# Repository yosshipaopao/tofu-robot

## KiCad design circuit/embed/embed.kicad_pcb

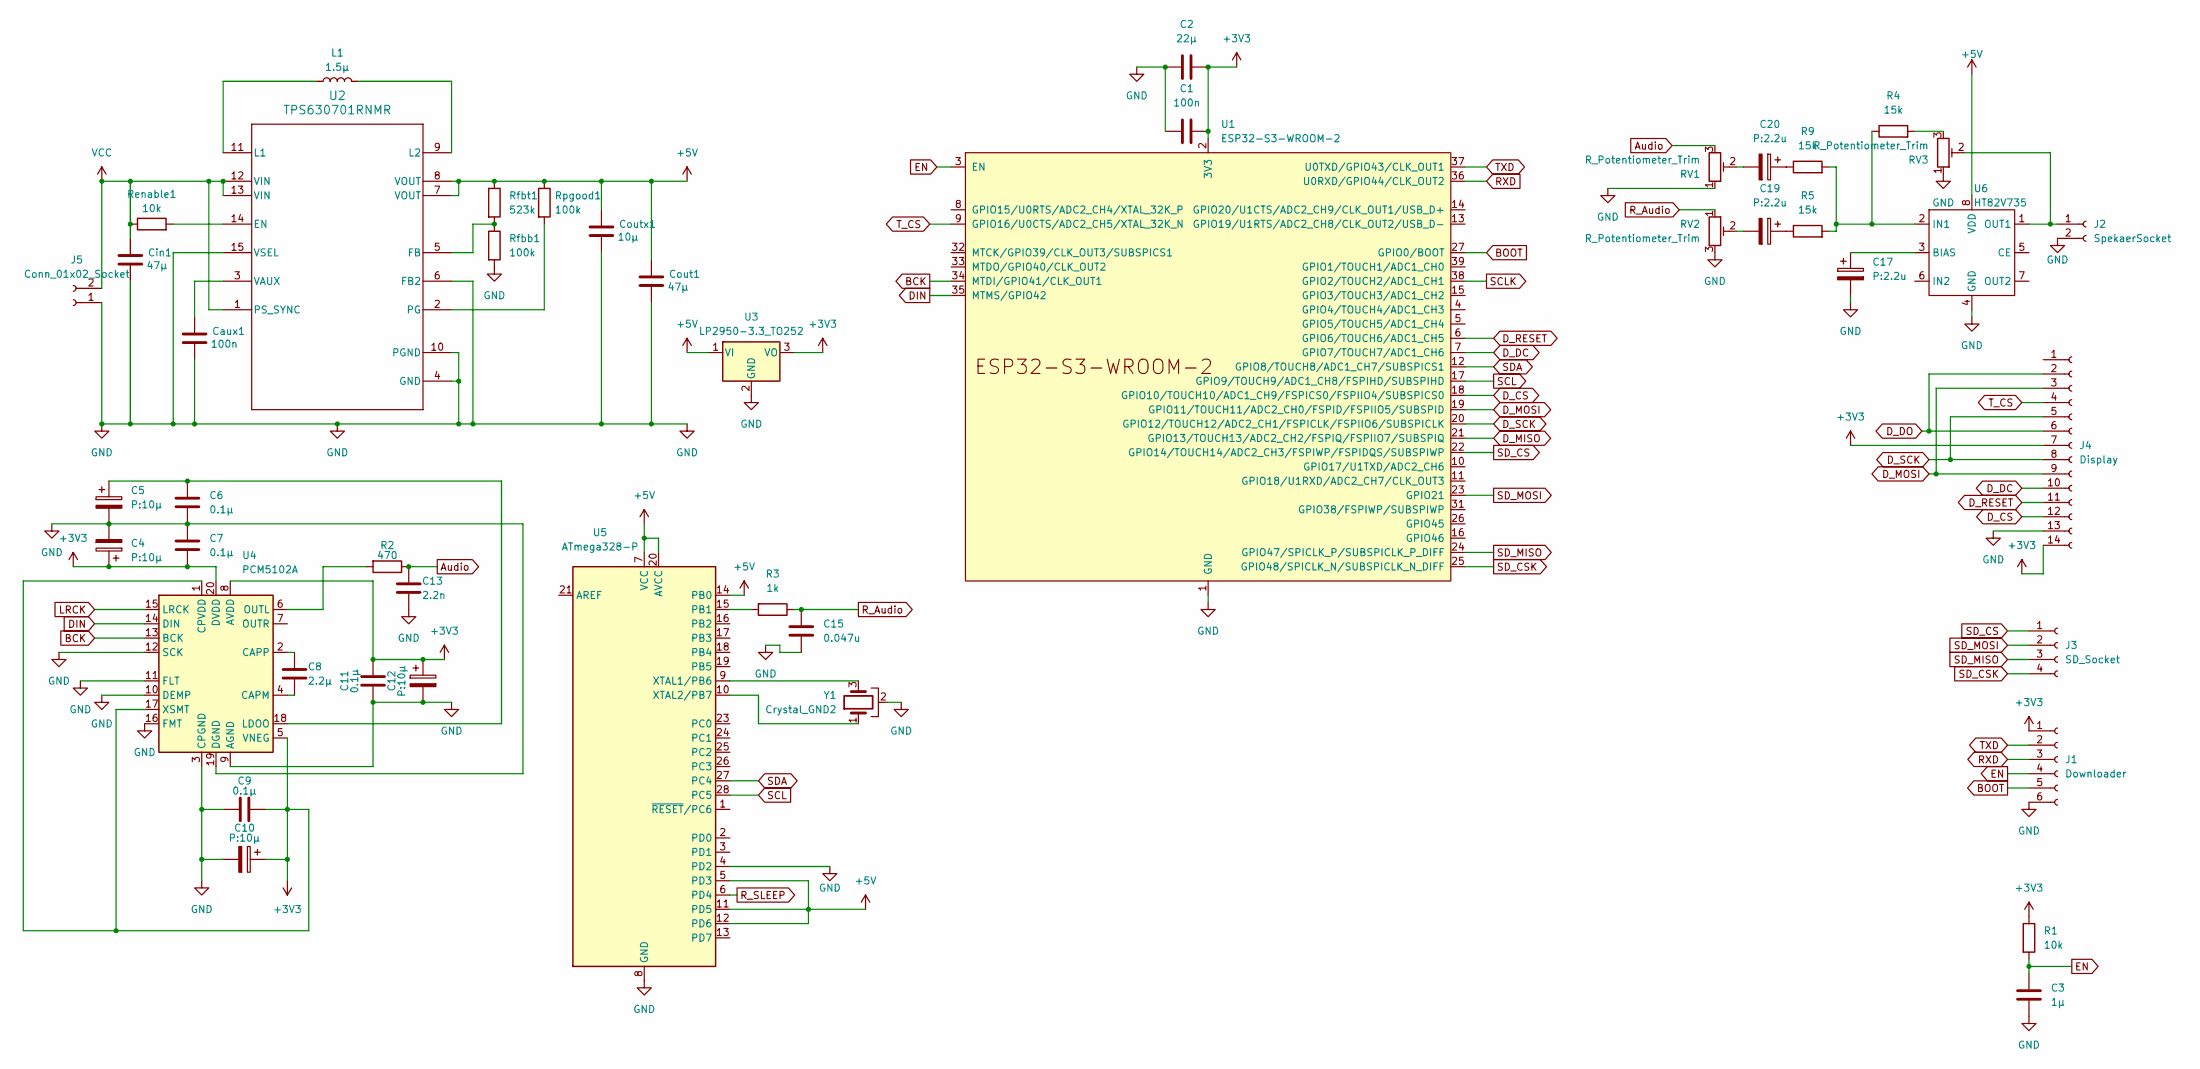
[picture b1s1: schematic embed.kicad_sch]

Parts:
C1: 100n; C_0402_1005Metric
C2: 22μ; C_0603_1608Metric
C3: 1μ; C_0402_1005Metric
C4, C5, C10, C12: P:10μ; CP_Elec_3x5.4
C6, C7, C9, C11: 0.1μ; C_0402_1005Metric
C8: 2.2μ; C_0504_1310Metric
C13: 2.2n; C_0402_1005Metric
C15: 0.047u; C_0402_1005Metric
C17, C19, C20: P:2.2u; CP_Elec_4x5.4
Caux1: 100n; C_0402_1005Metric
Cin1: 47μ; C_1210_3225Metric
Cout1: 47μ; C_1210_3225Metric
Coutx1: 10μ; C_0603_1608Metric
J1: Downloader; PinSocket_1x06_P2.54mm_Vertical
J2: SpekaerSocket; PinSocket_1x02_P2.54mm_Vertical
J3: SD_Socket; PinSocket_1x04_P2.54mm_Vertical
J4: Display; PinSocket_1x14_P2.54mm_Vertical
J5: Conn_01x02_Socket; PinHeader_1x02_P2.54mm_Vertical
L1: 1.5μ; L_Bourns_SRN8040TA
R1: 10k; R_0603_1608Metric
R2: 470; R_2010_5025Metric
R3: 1k; R_1210_3225Metric
R4, R5, R9: 15k; R_0603_1608Metric
RV1, RV2, RV3: R_Potentiometer_Trim; Potentiometer_Bourns_PRS11S_Vertical
Renable1: 10k; R_0201_0603Metric
Rfbb1: 100k; R_0603_1608Metric
Rfbt1: 523k; R_0603_1608Metric
Rpgood1: 100k; R_0603_1608Metric
U1: ESP32-S3-WROOM-2
U2: TPS630701RNMR; RNM0015A
U3: LP2950-3.3_TO252; TO-252-2
U4: PCM5102A; TSSOP-20_4.4x6.5mm_P0.65mm
U5: ATmega328-P; DIP-28_W7.62mm
U6: HT82V735; SOP8
Y1: Crystal_GND2; Resonator_Murata_CSTLSxxxX-3Pin_W5.5mm_H3.0mm

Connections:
+3V3: C1.1, C2.1, C4.1, C7.2, C9.1, C10.1, C11.1, C12.1, J1.1, J4.7, J4.14, R1.1, U1.2 (3V3), U3.3 (VO), U4.1 (CPVDD), U4.5 (VNEG), U4.8 (AVDD), U4.17 (XSMT), U4.20 (DVDD)
+5V: Cout1.1, Coutx1.1, Rfbt1.1, Rpgood1.1, U2.7 (VOUT), U2.8 (VOUT), U3.1 (VI), U5.5 (PD3), U5.7 (VCC), U5.11 (PD5), U5.12 (PD6), U5.14 (PB0), U5.20 (AVCC), U6.8 (VDD)
Audio: C13.1, R2.1, RV1.3
BCK: U1.34 (MTDI/GPIO41/CLK_OUT1), U4.13 (BCK)
BOOT: J1.5, U1.27 (GPIO0/BOOT)
DIN: U1.35 (MTMS/GPIO42), U4.14 (DIN)
D_CS: J4.12, U1.18 (GPIO10/TOUCH10/ADC1_CH9/FSPICS0/FSPIIO4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)
D_DC: J4.10, U1.7 (GPIO7/TOUCH7/ADC1_CH6)
D_DO: J4.2, J4.6
D_MISO: U1.21 (GPIO13/TOUCH13/ADC2_CH2/FSPIQ/FSPIIO7/S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)
D_MOSI: J4.3, J4.9, U1.19 (GPIO11/TOUCH11/ADC2_CH0/FSPID/FSPIIO5/S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)
D_RESET: J4.11, U1.6 (GPIO6/TOUCH6/ADC1_CH5)
D_SCK: J4.5, J4.8, U1.20 (GPIO12/TOUCH12/ADC2_CH1/FSPICLK/FSPIIO6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)
EN: C3.1, J1.4, R1.2, U1.3 (EN)
GND: C1.2, C2.2, C3.2, C4.2, C5.2, C6.2, C7.1, C9.2, C10.2, C11.2, C12.2, C13.2, C15.1, C17.2, Caux1.2, Cin1.2, Cout1.2, Coutx1.2, J1.6, J2.2, J4.13, J5.1, RV1.1, RV2.3, RV3.1, Rfbb1.2, U1.1 (GND), U1.40 (GND), U1.41 (GND), U2.4 (GND), U2.6 (FB2), U2.10 (PGND), U2.15 (VSEL), U3.2 (GND), U4.3 (CPGND), U4.9 (AGND), U4.10 (DEMP), U4.11 (FLT), U4.12 (SCK), U4.16 (FMT), U4.19 (DGND), U5.4 (PD2), U5.8 (GND), U5.22 (GND), U6.4 (GND), Y1.2
LRCK: U4.15 (LRCK)
unnamed: C19.1, R5.1
unnamed: C19.2, RV2.2
unnamed: C20.1, R9.1
unnamed: C20.2, RV1.2
unnamed: J2.1, RV3.2, U6.1 (OUT1)
unnamed: R4.2, RV3.3
unnamed: Renable1.2, U2.14 (EN)
unnamed: Rfbb1.1, Rfbt1.2, U2.5 (FB)
unnamed: L1.1, U2.11 (L1)
unnamed: L1.2, U2.9 (L2)
unnamed: Rpgood1.2, U2.2 (PG)
unnamed: Caux1.1, U2.3 (VAUX)
unnamed: C8.2, U4.4 (CAPM)
unnamed: C8.1, U4.2 (CAPP)
unnamed: C5.1, C6.1, U4.18 (LDOO)
unnamed: R2.2, U4.6 (OUTL)
unnamed: R3.2, U5.15 (PB1)
unnamed: U5.9 (XTAL1/PB6), Y1.3
unnamed: U5.10 (XTAL2/PB7), Y1.1
unnamed: C17.1, U6.3 (BIAS)
unnamed: R4.1, R5.2, R9.2, U6.2 (IN1)
RXD: J1.3, U1.36 (U0RXD/GPIO44/CLK_OUT2)
R_Audio: C15.2, R3.1, RV2.1
R_SLEEP: U5.6 (PD4)
SCL: U1.17 (GPIO9/TOUCH9/ADC1_CH8/FSPIHD/SUBSPIHD), U5.28 (PC5)
SCLK: U1.38 (GPIO2/TOUCH2/ADC1_CH1)
SDA: U1.12 (GPIO8/TOUCH8/ADC1_CH7/SUBSPICS1), U5.27 (PC4)
SD_CS: J3.1, U1.22 (GPIO14/TOUCH14/ADC2_CH3/FSPIWP/FSPIDQS/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)
SD_CSK: J3.4, U1.25 (GPIO48/SPICLK_N/SUBSPICLK_N_DIFF)
SD_MISO: J3.3, U1.24 (GPIO47/SPICLK_P/SUBSPICLK_P_DIFF)
SD_MOSI: J3.2, U1.23 (GPIO21)
TXD: J1.2, U1.37 (U0TXD/GPIO43/CLK_OUT1)
T_CS: J4.4, U1.9 (GPIO16/U0CTS/ADC2_CH5/XTAL_32K_N)
VCC: Cin1.1, J5.2, Renable1.1, U2.1 (PS_SYNC), U2.12 (VIN), U2.13 (VIN)

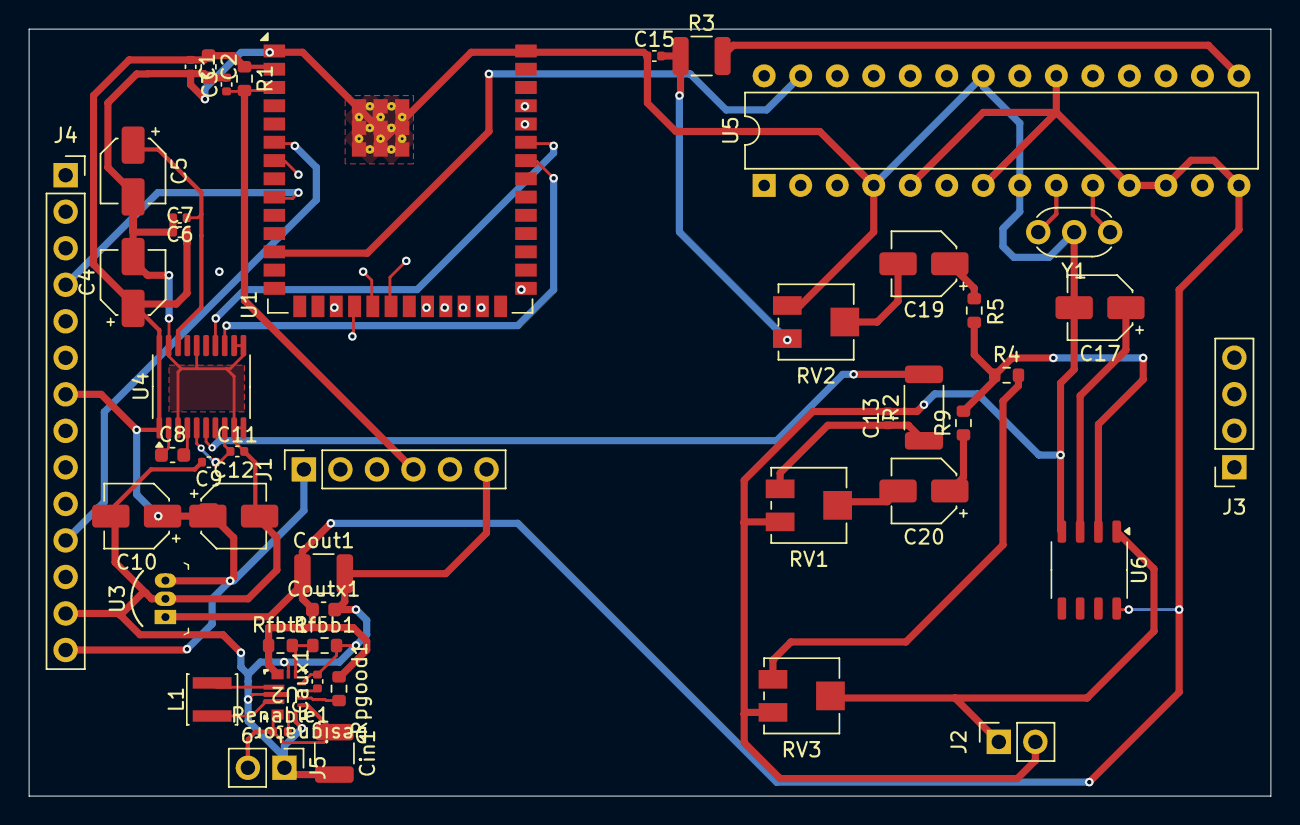
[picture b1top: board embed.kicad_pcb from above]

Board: 4 copper layers, 86.4 x 53.3 mm, 47 parts (0 on the bottom side), 46 nets.

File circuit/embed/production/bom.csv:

Designator,Footprint,Quantity,Value,LCSC Part #
"C1, Caux1",0402,2,100n,
"C10, C12, C4, C5",CP_Elec_4x5.4,4,P:10μ,
"C11, C6, C7, C9",0402,4,0.1μ,
C13,0402,1,2.2n,
C15,0402,1,0.047u,
"C17, C19, C20",CP_Elec_4x5.4,3,P:2.2u,
C2,0603,1,22μ,
C3,0402,1,1μ,
C8,0603,1,2.2μ,
"Cin1, Cout1",1210,2,47μ,
Coutx1,0603,1,10μ,
J1,PinSocket_1x06_P2.54mm_Vertical,1,Downloader,
J2,PinSocket_1x02_P2.54mm_Vertical,1,SpekaerSocket,
J3,PinSocket_1x04_P2.54mm_Vertical,1,SD_Socket,
J4,PinSocket_1x14_P2.54mm_Vertical,1,Display,
J5,PinHeader_1x02_P2.54mm_Vertical,1,Conn_01x02_Socket,
L1,L_Sunlord_SWPA3015S,1,1.5μ,
R1,0603,1,10k,
R2,2010,1,470,
R3,1210,1,1k,
"R4, R5, R9",0603,3,15k,
"RV1, RV2, RV3",Potentiometer_Vishay_TS53YJ_Vertical,3,R_Potentiometer_Trim,
Renable1,0402,1,10k,
"Rfbb1, Rpgood1",0603,2,100k,
Rfbt1,0603,1,523k,
U1,ESP32-S3-WROOM-2,1,ESP32-S3-WROOM-2,
U2,RNM0015A,1,TPS630701RNMR,
U3,TO-92-3,1,LP2950-3.3_TO252,
U4,TSSOP-20_4.4x6.5mm_P0.65mm,1,PCM5102A,
U5,DIP-28_W7.62mm,1,ATmega328-P,
U6,SSOP-8_3.9x5.05mm_P1.27mm,1,HT82V735,
Y1,Resonator_Murata_CSTLSxxxX-3Pin_W5.5mm_H3.0mm,1,Crystal_GND2,

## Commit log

2024-06-01 init
2024-06-02 add assets
2024-06-02 run in multithread
2024-06-02 update name
2024-06-02 wtf?
2024-10-06 apply
